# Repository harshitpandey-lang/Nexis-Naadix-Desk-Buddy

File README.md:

# Nexis

Nexis is a dual AI powered desk automation bot which uses raspberry pi to run a local llm and also uses a cloud deployed ai agent to do the tasks given to it in small chunks. We can give instructions through the interactive touch screen and also through the micophone. 
It uses esp32 to give commands to the device connected through the USB. 

## Overview

Nexis is a desk buddy which can do all sort of works upon good training and customisation. It uses a raspberry pi and open source AI model to break works into smaller steps. It uses the the local llm to generte the HID code respective to every step given uses python to asses if the work is performed then goes ahed with next step till all are completed. 
It uses esp32 to give HID code to the PC connected to make it do or perform a particular task. It can communicate or given instructionthrough the Touchscreen and Microphone.

---

## System Architecture
User

 │
 
 ├── Voice Input
 
 ├── Touchscreen Input
 
 │
 
 ▼
 
Raspberry Pi 4

 │
 
 ├── Local LLM
 
 ├── Task Planner
 
 ├── Verification Engine
 
 └── Cloud AI Agent
 
 │
 
 ▼
 
ESP32-S3 HID Controller

 │
 
 ▼
 
Connected Computer

 │
 
 ├── Keyboard Events
 
 ├── Mouse Events
 
 └── Workflow Execution

## Specifications

| Parameters | Value |
| Code | Python|
| Hardware | Raspberry pi model B |
| Design | 3d printed and rubber keys|

### Hardware

| Component | Purpose |
|-----------|---------|
| Raspberry Pi 4 Model B | Main computing unit |
| Official Raspberry Pi Display | User interface |
| ESP32-S3 | HID controller |
| INMP441 Microphone | Voice input |
| MAX98357A Amplifier | Audio output |
| Speaker | Voice feedback |
| Rotary Encoder | Navigation control |
| Push Buttons | User interaction |
| LiPo Battery | Portable power |

See BOM.md for the complete bill of materials.

---

## Software

- Backend Language
  - Python
- Framework
  - FastAPI
- AI
  - OpenAI API
  - Claude API
  - Gemini API
- Data Models
  - Pydantic
- Hosting
  - Render

### Raspberry Pi

Install:

* Raspberry Pi OS
* Python
* Git
* Required libraries

### ESP32

Install:

* Arduino IDE or PlatformIO
* ESP32 Board Package

---

### How It Works
- User gives an instruction.
- Nexis interprets the request.
- AI breaks the task into smaller steps.
- Local verification checks progress.
- ESP32 receives generated HID commands.
- Commands are executed on the connected computer.
- Nexis confirms completion and proceeds to the next step.

This process continues until the entire workflow is completed.

---

## Gallery

## Future Improvements

- It can work as full work automation
- It can also control the other tech stacks of your rooms
- If developed correctly it can do the job of any person

## Acknowledgement

- The raspberrry pi model 4 was alloted by my college (Jaypee Institute of Information Technology), which I am grateful.
- I am grateful for the oppurtunity presented by the Hack Club called fallout, Which I am a part of and am proud of making this project under their guidance for more reference realted to the fallout event (https://fallout.hackclub.com/path).
- I am also grateful for the help given by my seniors.

---
# Zine page

---

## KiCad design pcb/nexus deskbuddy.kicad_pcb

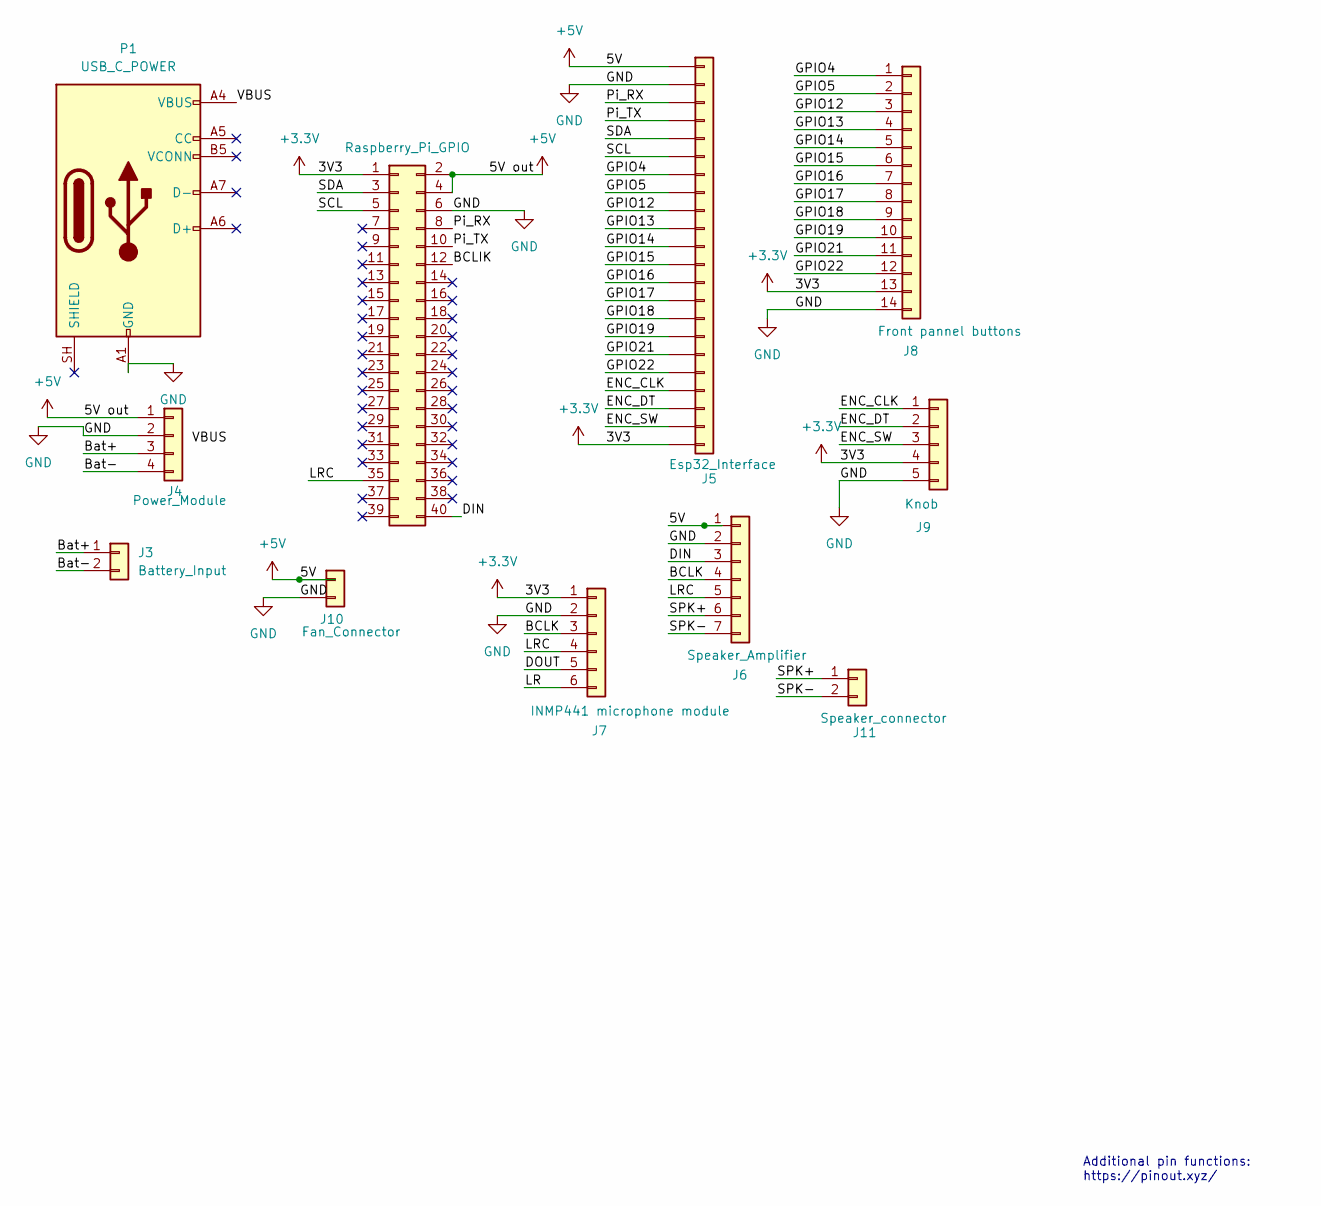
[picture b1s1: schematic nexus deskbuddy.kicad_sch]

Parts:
J2: Raspberry_Pi_GPIO; PinHeader_2x20_P2.54mm_Horizontal
J3: Battery_Input; JST_PH_B2B-PH-K_1x02_P2.00mm_Vertical
J4: Power_Module; FanPinHeader_1x04_P2.54mm_Vertical
J5: Esp32_Interface; PinHeader_1x22_P2.54mm_Horizontal
J6: Speaker_Amplifier; PinHeader_1x07_P2.54mm_Vertical
J7: INMP441 microphone module; PinHeader_1x06_P2.54mm_Vertical
J8: Front pannel buttons; PinHeader_1x14_P2.54mm_Horizontal
J9: Knob; PinHeader_1x05_P2.54mm_Horizontal
J10: Fan_Connector; PinHeader_1x02_P2.54mm_Horizontal
J11: Speaker_connector; PinHeader_1x02_P1.00mm_Horizontal
P1: USB_C_POWER; USB_C_Receptacle_Amphenol_124019772112A

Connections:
+3.3V: J2.1, J5.22, J7.1, J8.13, J9.4
+5V: J2.2, J2.4, J4.1, J5.1, J6.1, J10.1
/BCLIK: J2.12
/BCLK: J6.4, J7.3
/Bat+: J3.1, J4.3
/Bat-: J3.2, J4.4
/DIN: J2.40, J6.3
/DOUT: J7.5
/ENC_CLK: J5.19, J9.1
/ENC_DT: J5.20, J9.2
/ENC_SW: J5.21, J9.3
/GPIO4: J5.7, J8.1
/GPIO5: J5.8, J8.2
/GPIO12: J5.9, J8.3
/GPIO13: J5.10, J8.4
/GPIO14: J5.11, J8.5
/GPIO15: J5.12, J8.6
/GPIO16: J5.13, J8.7
/GPIO17: J5.14, J8.8
/GPIO18: J5.15, J8.9
/GPIO19: J5.16, J8.10
/GPIO21: J5.17, J8.11
/GPIO22: J5.18, J8.12
/LR: J7.6
/LRC: J2.35, J6.5, J7.4
/Pi_RX: J2.8, J5.3
/Pi_TX: J2.10, J5.4
/SCL: J2.5, J5.6
/SDA: J2.3, J5.5
/SPK+: J6.6, J11.1
/SPK-: J6.7, J11.2
/VBUS: P1.A4 (VBUS), P1.A9 (VBUS), P1.B4 (VBUS), P1.B9 (VBUS)
GND: J2.6, J4.2, J5.2, J6.2, J7.2, J8.14, J9.5, J10.2, P1.A1 (GND), P1.A12 (GND), P1.B1 (GND), P1.B12 (GND)

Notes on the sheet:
Additional pin functions: https://pinout.xyz/

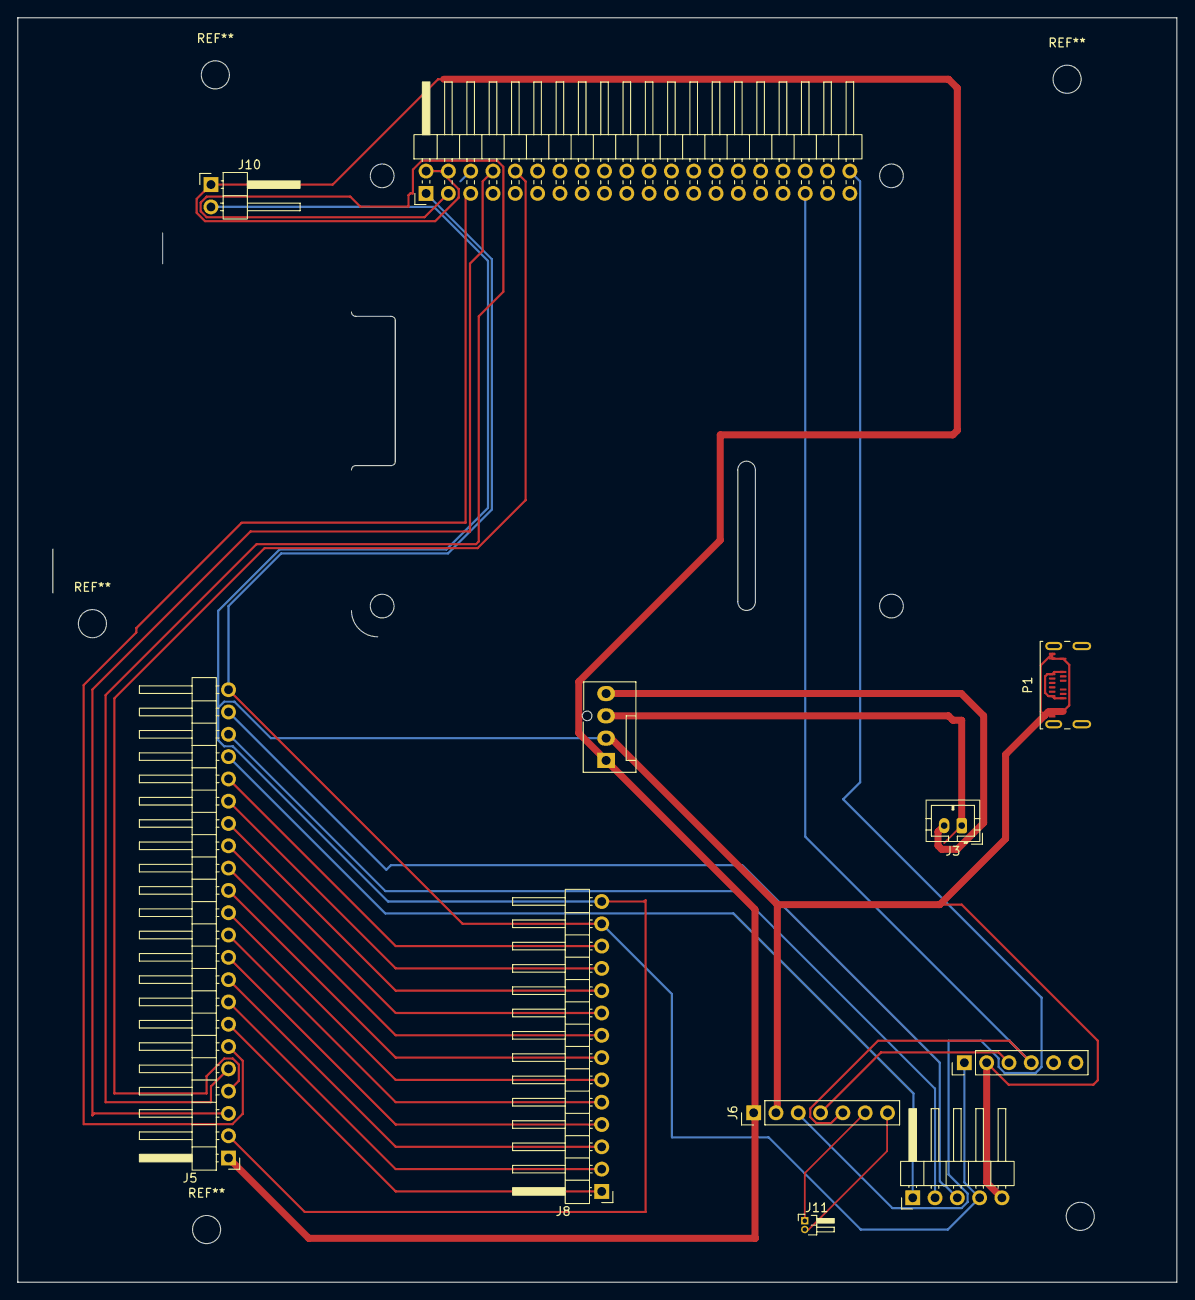
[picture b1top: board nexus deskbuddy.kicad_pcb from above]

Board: 2 copper layers, 132.0 x 144.0 mm, 15 parts (0 on the bottom side), 30 nets.

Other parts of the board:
MH1, MH2, MH3, MH4: MountingHole_2.7mm_M2.5

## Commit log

2026-05-30 Create FIRMWARE>md
2026-05-30 Create OAi
2026-05-30 Create deleteit later
2026-06-05 Revise README with new sections and content
    Updated hardware and software sections, added acknowledgments and future improvements.
2026-06-05 Enhance README with gallery and future improvements
    Added a gallery section with images and future improvements.
